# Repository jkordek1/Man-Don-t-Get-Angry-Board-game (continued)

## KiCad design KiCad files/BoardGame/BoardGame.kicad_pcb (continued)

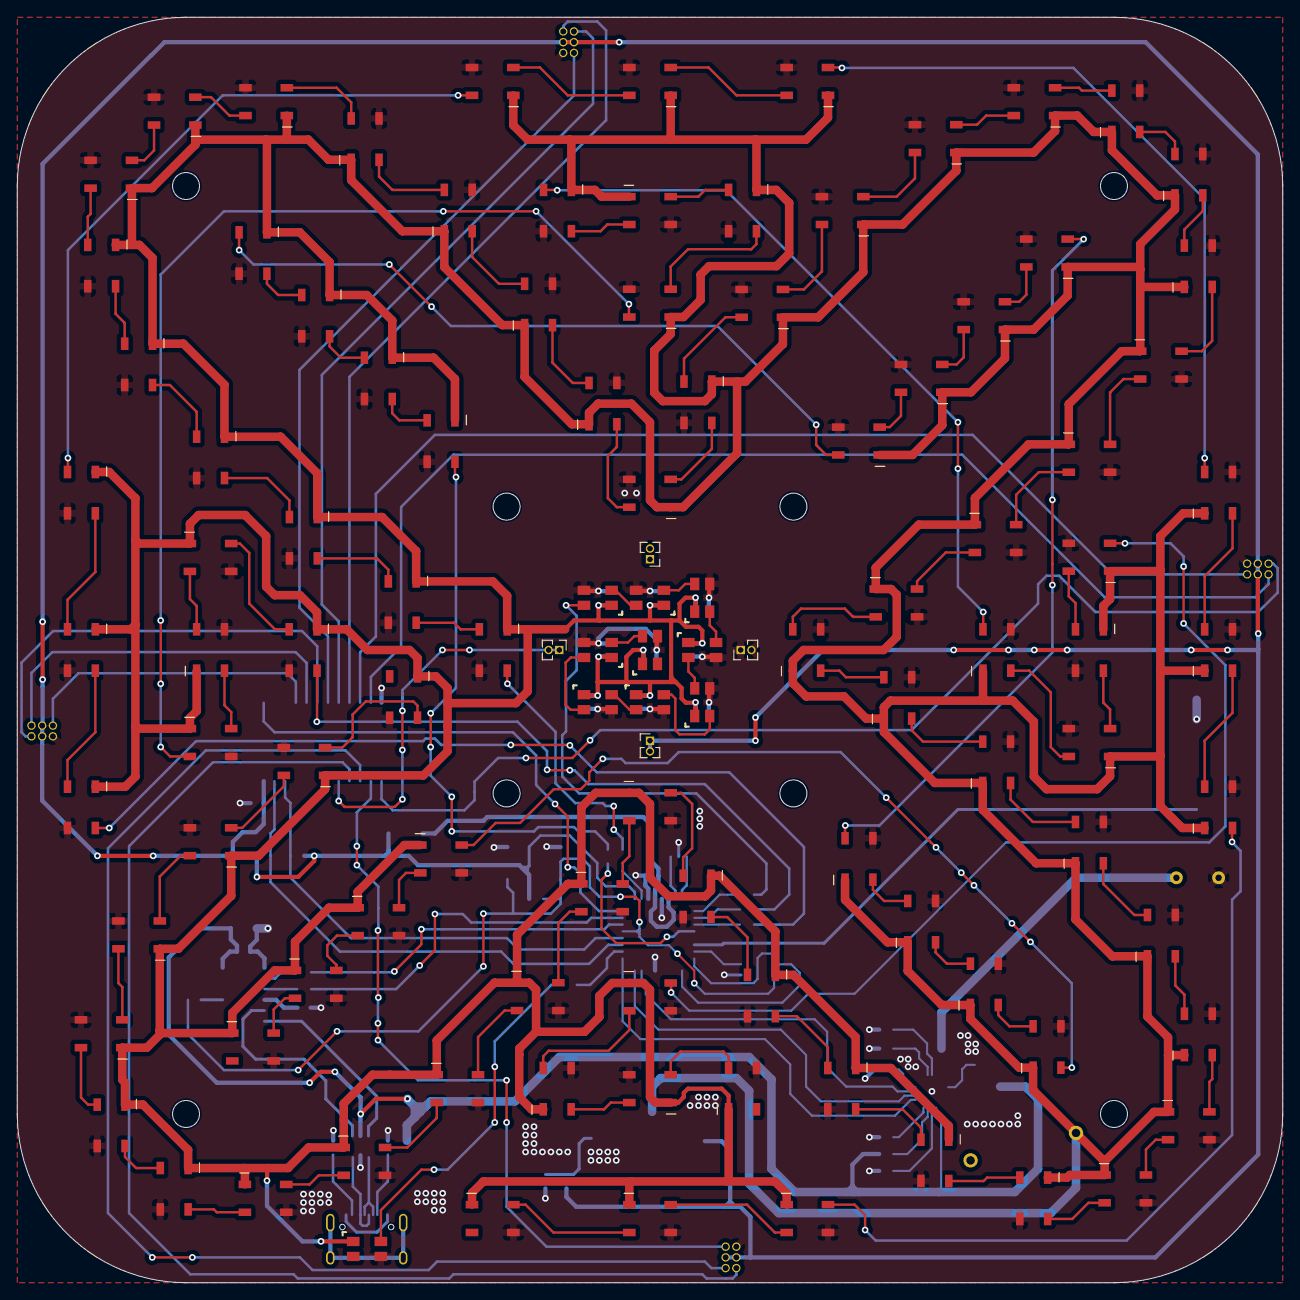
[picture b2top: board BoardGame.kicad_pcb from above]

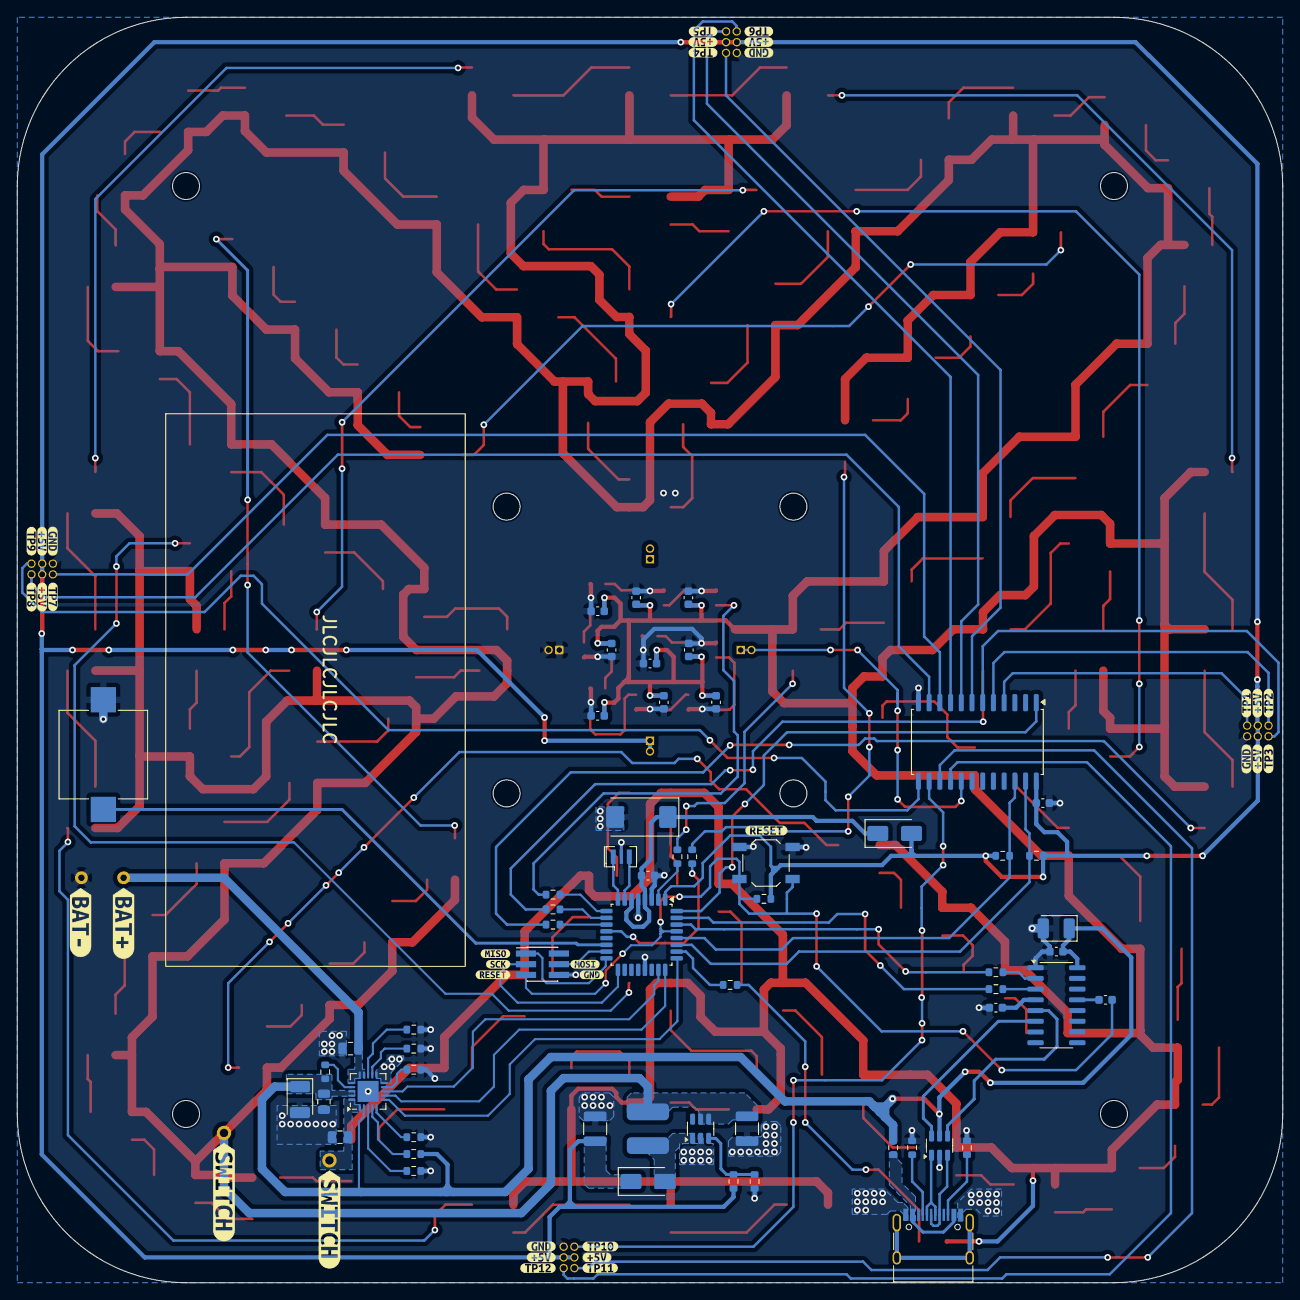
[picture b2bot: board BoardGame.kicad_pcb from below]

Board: 2 copper layers, 150.0 x 150.0 mm, 218 parts (94 on the bottom side), 167 nets.

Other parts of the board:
kibuzzard-635B9A1E, kibuzzard-635B9A1E#2: G***; kibuzzard-635B9A1E
kibuzzard-635BA7B4: G***; kibuzzard-635BA7B4
kibuzzard-635BA762: G***; kibuzzard-635BA762
kibuzzard-635CF4BC: G***; kibuzzard-635CF4BC
kibuzzard-635CF4CF: G***; kibuzzard-635CF4CF
kibuzzard-635CF4E4: G***; kibuzzard-635CF4E4
kibuzzard-635CF6FA, kibuzzard-635CF6FA#2, kibuzzard-635CF6FA#3, kibuzzard-635CF6FA#4: G***; kibuzzard-635CF6FA
kibuzzard-635CF7DB: G***; kibuzzard-635CF7DB
kibuzzard-635CF483: G***; kibuzzard-635CF483
kibuzzard-635CF507: G***; kibuzzard-635CF507
kibuzzard-635CF752, kibuzzard-635CF752#2, kibuzzard-635CF752#3, kibuzzard-635CF752#4, kibuzzard-635CF752#5, kibuzzard-635CF752#6, kibuzzard-635CF752#7, kibuzzard-635CF752#8: G***; kibuzzard-635CF752
kibuzzard-635CF795: G***; kibuzzard-635CF795
kibuzzard-635CF884: G***; kibuzzard-635CF884
kibuzzard-635CFA5F: G***; kibuzzard-635CFA5F
kibuzzard-635CFA8A: G***; kibuzzard-635CFA8A
kibuzzard-635CFAA6: G***; kibuzzard-635CFAA6
kibuzzard-635CFAF1: G***; kibuzzard-635CFAF1
kibuzzard-635CFB05: G***; kibuzzard-635CFB05
kibuzzard-635CFB13: G***; kibuzzard-635CFB13
kibuzzard-635CFD4A: G***; kibuzzard-635CFD4A
kibuzzard-635CFDAF: G***; kibuzzard-635CFDAF
kibuzzard-635CFDBF: G***; kibuzzard-635CFDBF
kibuzzard-636375F6: G***; kibuzzard-636375F6

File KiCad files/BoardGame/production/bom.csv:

Designator,Footprint,Quantity,Value,LCSC Part #
BT301,battery_103565_3000mah,1,Battery_Cell,-
"C1001, C1002, C1003, C1004, C1005, C1006, C1007, C1008, C1009, C201, C202, C204, C401, C501",0603,14,100n,C113803
C203,CP_EIA-3528-21_Kemet-B,1,10u,C2798040
C301,CP_EIA-3528-21_Kemet-B,1,4u7/25V,C2798040
"C302, C303, C304",0805,3,10u,C237493
C502,CP_EIA-7343-31_Kemet-D,1,1500uF,
"C601, C602",1210,2,22u / 16V,C337451
"D1001, D1002, D1003, D1004, D1005, D1006, D1007, D1008, D1009, D1010, D1011, D1012, D1013, D1014, D1015, D1016, D1017, D1018, D1019, D1020, D1021, D1022, D1023, D1024, D1025, D1026, D1027, D1028, D1029, D1030, D1031, D1032, D1033, D1034, D1035, D1036, D1037, D1038, D1039, D1040, D1041, D1042, D1043, D1044, D1045, D1046, D1047, D1048, D1049, D1050, D1051, D1052, D1053, D1054, D1055, D1056, D1057, D1058, D1059, D1060, D1061, D1062, D1063, D1064, D1065, D1066, D1067, D1068, D1069, D1070, D1071, D1072, D1073, D1074, D1075, D1076, D1077, D1078, D1079, D1080, D1081, D1082, D1083, D1084, D1085, D1086, D1087, D1088, D1089, D1090, D1091, D1092, D1093, D1094, D1095, D1096",LED_WS2812B_edited,96,WS2812B,-
"D1097, D1098, D1099, D1100, D1101, D1102, D1103, D1104, D1105",WS2812-mini,9,WS2812B,C527089
D1106,WS2812-mini,1,WS2812B,-
"D501, D601",D_SMA,2,SS12,C2985002
FB201,0603,1,100 @ 100MHz,C107332
"H1001, H1002, H1003, H1004, H1005, H1006, H1007, H1008",MountingHole_3.2mm_M3,8,MountingHole,
J201,USB_C_Receptacle_HRO_TYPE-C-31-M-12,1,USB_C_Receptacle_USB2.0,-
"J301, J302",PinHeader_1x01,2,Conn_01x01,-
"J401, J402, J403, J404",2x03_P1.27mm_conn,4,Conn_02x03_Odd_Even,-
"J405, J406, J407, J408",PinHeader_1x02_P1.27mm_Vertical,4,Conn_01x02_Female,
J501,PinHeader_2x03_P1.27mm_Vertical_SMD,1,USBasp,-
L601,Inductor_4mm(5x5mm pads),1,4R7,
LS501,KLJ-1102,1,Buzzer,
"R1001, R1002, R1003, R1004, R1005, R1006",0603,6,470R,
"R201, R204",0603,2,1k,
"R202, R203",0603,2,5k1,C3017721
"R301, R303, R307, R308, R310, R501",0603,6,10k,
R302,0603,1,2k,C25590
"R305, R601",0603,2,100k,
"R401, R402",0603,2,4k7,C114662
R602,0603,1,13k3,C185373
SW501,SW_SPST_TL3342,1,SW_Push,C2886894
U201,SOT-23-6,1,USBLC6-2SC6,C3029034
U202,SOIC-16_3.9x9.9mm_P1.27mm,1,CH340C,
U301,QFN-20-1EP_4x4mm_P0.5mm_EP2.5x2.5mm,1,MCP73871-2CC,
U401,SOIC-24W_7.5x15.4mm_P1.27mm,1,PCF8575,
U501,TQFP-32_7x7mm_P0.8mm,1,ATmega328P-A,
U601,SOT-23-6,1,MT3608,C2932326
Y501,CSTCE16M0V53-R0,1,16MHz,C32180

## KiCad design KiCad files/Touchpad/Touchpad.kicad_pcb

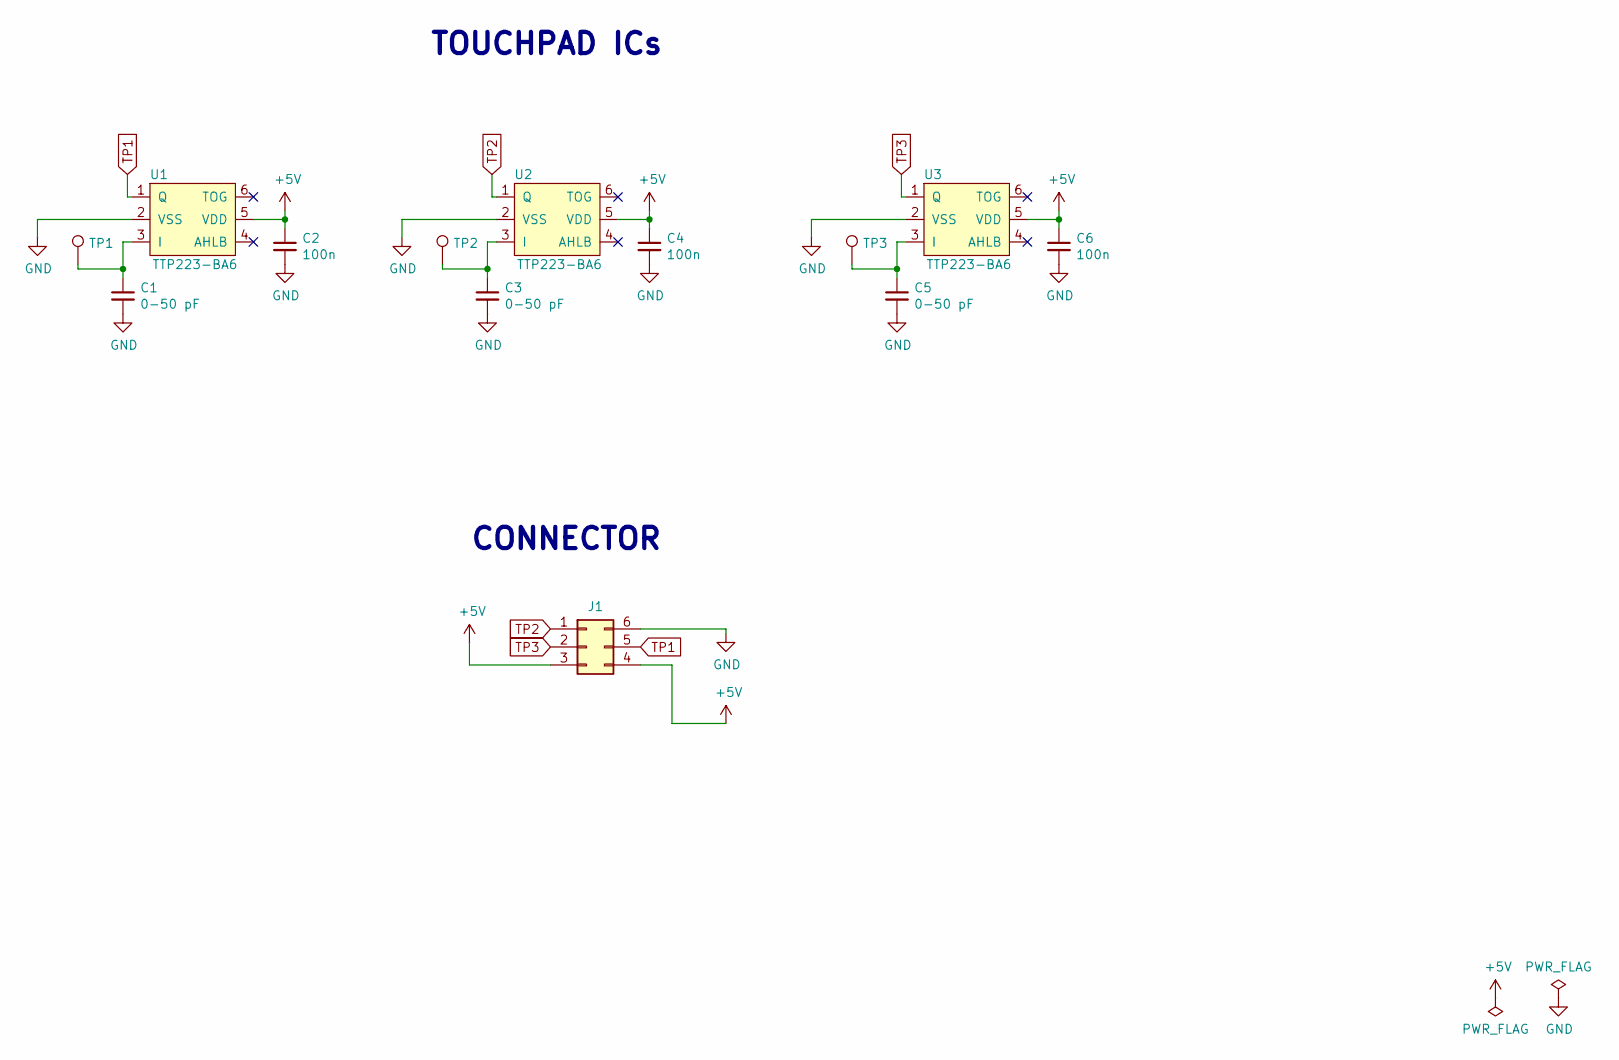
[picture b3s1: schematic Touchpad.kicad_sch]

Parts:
C1, C3, C5: 0-50 pF; C_0603_1608Metric
C2, C4, C6: 100n; C_0603_1608Metric
J1: Conn_02x03_Counter_Clockwise; PinHeader_2x03_P1.27mm_Vertical_SMD
TP1: TestPoint; TP_11mm_kvacica
TP2: TestPoint; TP_11mm_strelicaLijevo
TP3: TestPoint; TP_11mm_strelicaDesno
U1, U2, U3: TTP223-BA6; SOT-23-6

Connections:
+5V: C2.1, C4.1, C6.1, J1.3, J1.4, U1.5 (VDD), U2.5 (VDD), U3.5 (VDD)
GND: C1.2, C2.2, C3.2, C4.2, C5.2, C6.2, J1.6, U1.2 (VSS), U2.2 (VSS), U3.2 (VSS)
unnamed: C1.1, TP1.1, U1.3 (I)
unnamed: C3.1, TP2.1, U2.3 (I)
unnamed: C5.1, TP3.1, U3.3 (I)
TP1: J1.5, U1.1 (Q)
TP2: J1.1, U2.1 (Q)
TP3: J1.2, U3.1 (Q)

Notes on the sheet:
TOUCHPAD ICs
CONNECTOR

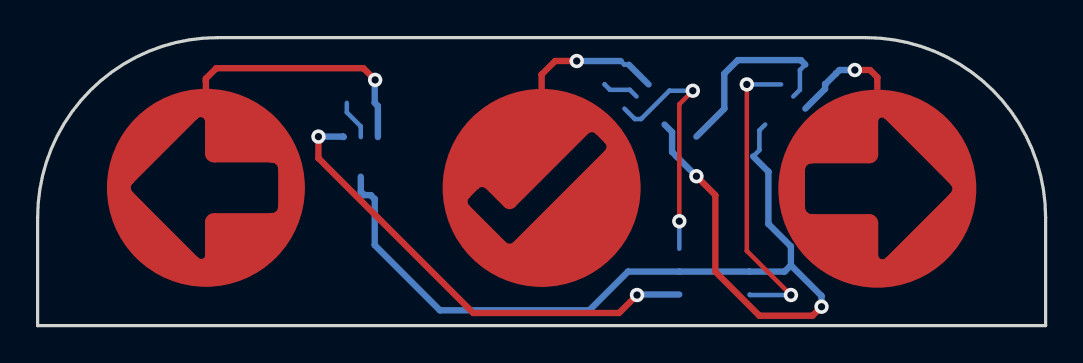
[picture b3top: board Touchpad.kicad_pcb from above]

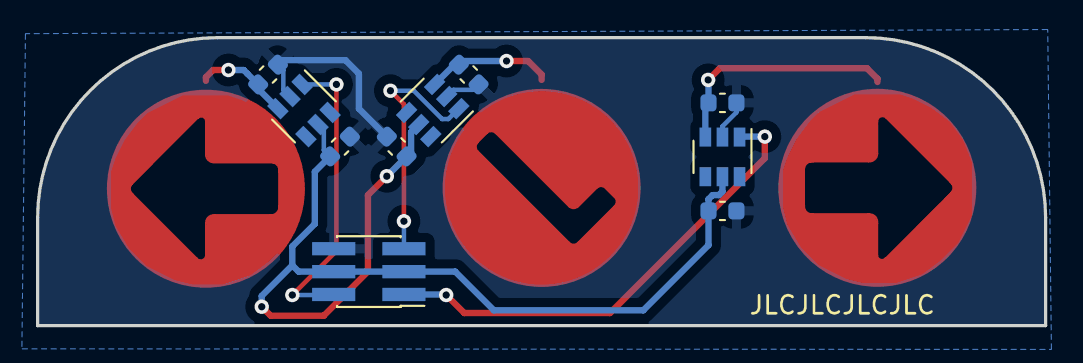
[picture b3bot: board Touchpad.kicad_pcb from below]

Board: 2 copper layers, 56.0 x 16.0 mm, 13 parts (10 on the bottom side), 8 nets.

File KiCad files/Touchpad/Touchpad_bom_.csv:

Component,Description,Part,References,Value,Footprint,Quantity Per PCB,Datasheet
1,"Unpolarized capacitor, small symbol",C_Small,C2 C4 C6,100n,C_0603_1608Metric,3,~
2,"Unpolarized capacitor, small symbol",C_Small,C1 C3 C5,0-50 pF,C_0603_1608Metric,3,~
3,"Generic connector, double row, 02x03, counter clockwise pin numbering scheme (similar to DIP packge numbering), script generated (kicad-library-utils/schlib/autogen/connector/)",Conn_02x03_Counter_Clockwise,J1,Conn_02x03_Counter_Clockwise,PinHeader_2x03_P1.27mm_Vertical_SMD,1,~
4,,TTP223-BA6,U1 U2 U3,TTP223-BA6,SOT-23-6,3,





Component Groups:,4
Component Count:,10
Fitted Components:,10
Number of PCBs:,1
Total components:,10
Schematic Version:,
Schematic Date:,
PCB Variant:,default
BoM Date:,10.1.2023. 13:06:24
Schematic Source:,Touchpad.kicad_sch
KiCad Version:,Eeschema (6.0.10)

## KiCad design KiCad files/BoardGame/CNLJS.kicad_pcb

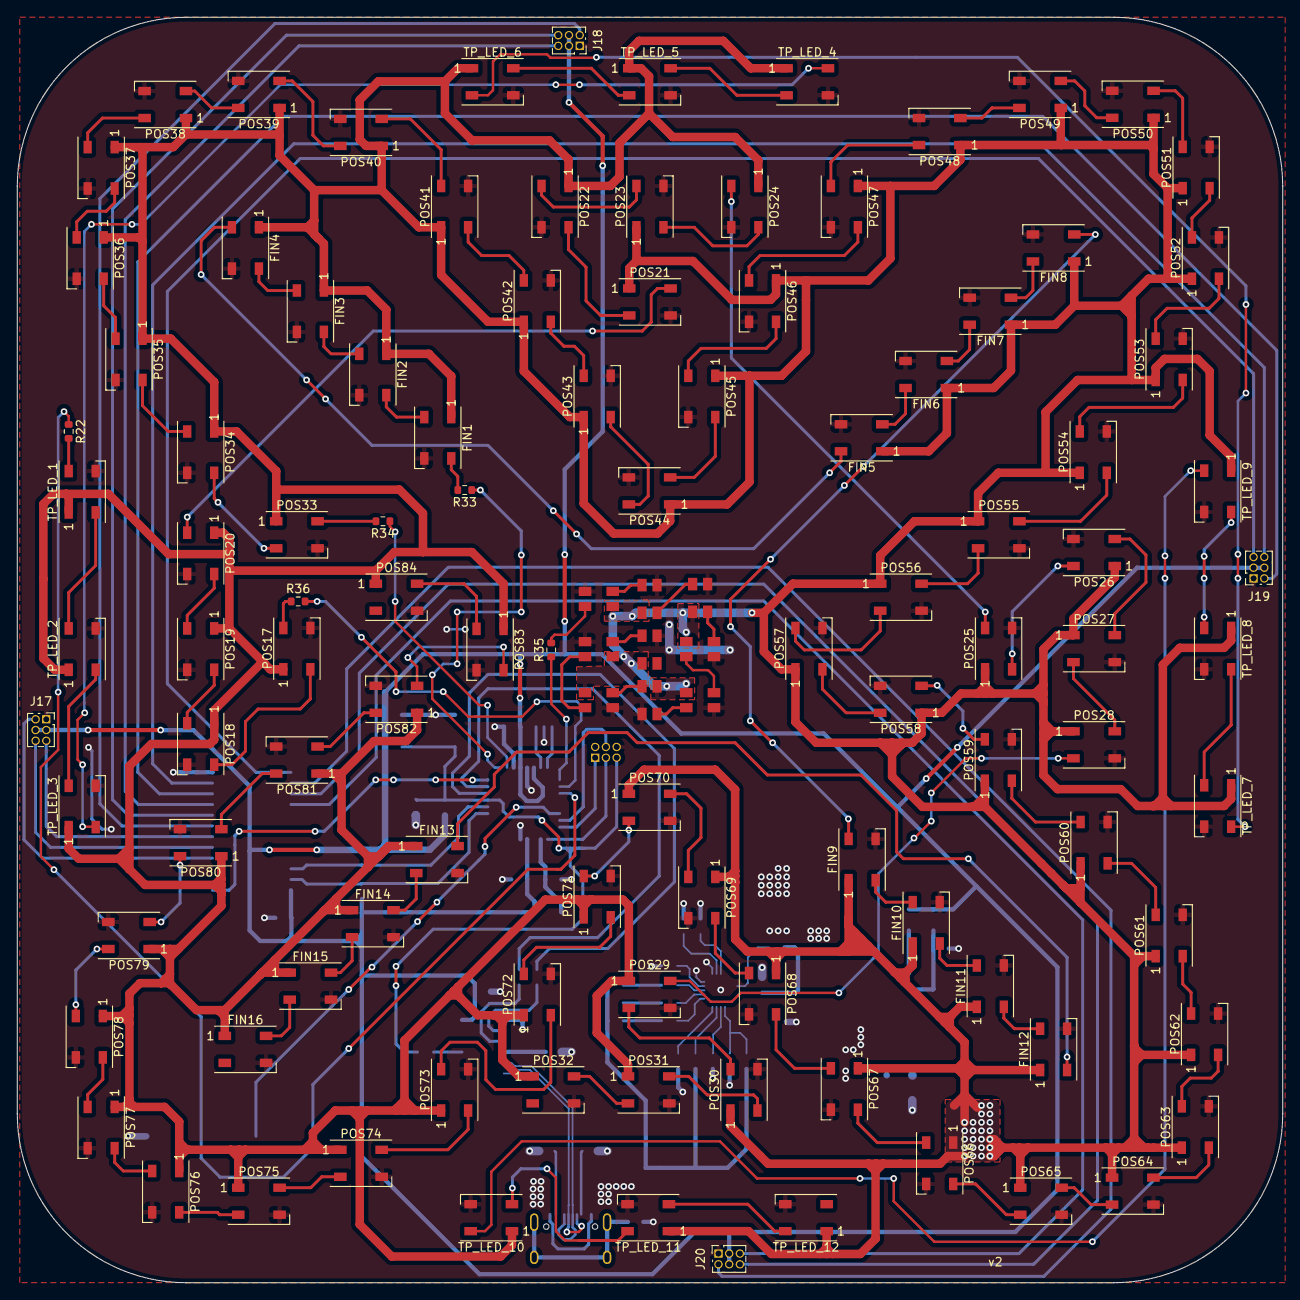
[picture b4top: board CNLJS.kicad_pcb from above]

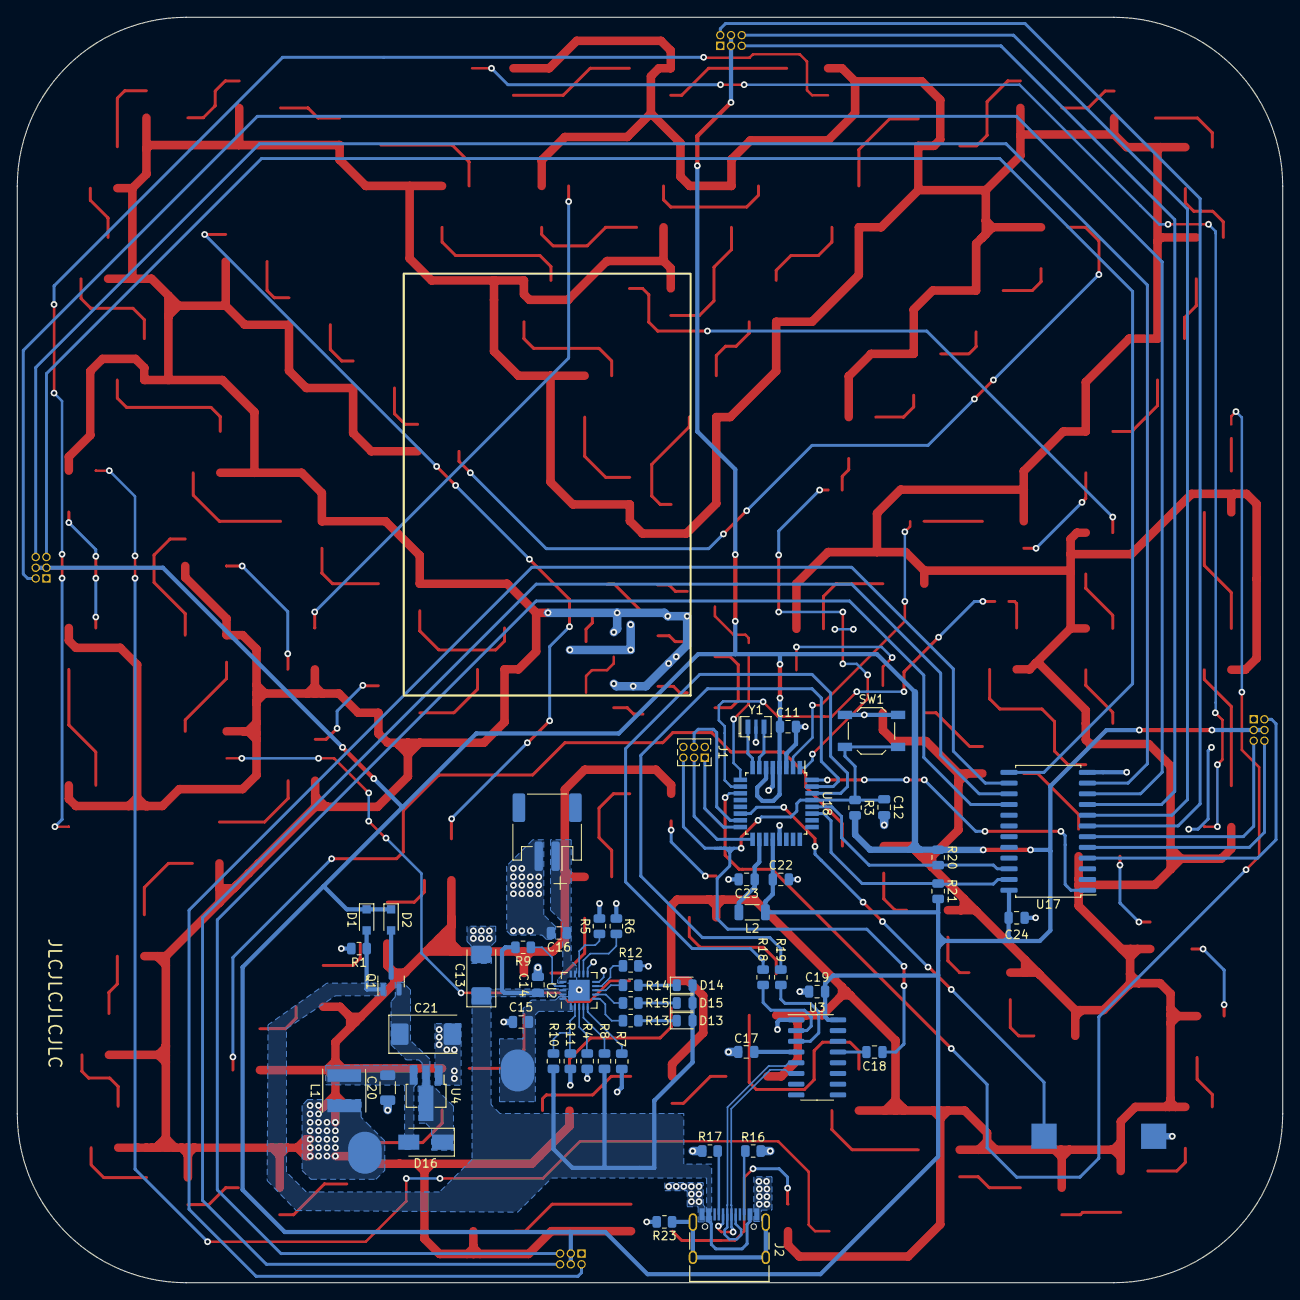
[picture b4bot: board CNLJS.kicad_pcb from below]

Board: 2 copper layers, 150.0 x 150.0 mm, 171 parts (57 on the bottom side), 167 nets.

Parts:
BT1: Battery_Cell; JST_PH_S2B-PH-SM4-TB_1x02-1MP_P2.00mm_Horizontal
C11, C18, C19, C22, C23, C24: 100n; C_0805_2012Metric
C12: 1u; C_0805_2012Metric
C13: 4.7u / 25V; CP_EIA-6032-28_Kemet-C
C14, C15, C16: 10u; C_0805_2012Metric
C17: 10n; C_0805_2012Metric
C20: 47u; C_1206_3216Metric
C21: 47u / 10V; CP_EIA-7343-30_AVX-N
D1, D2: B5819WS; D_SOD-323_HandSoldering
D13, D14, D15: LED_Small; LED_0805_2012Metric
D16: SS14; D_SMA
FIN1, FIN2, FIN3, FIN4, FIN5, FIN6, FIN7, FIN8, FIN9, FIN10, FIN11, FIN12, FIN13, FIN14, FIN15, FIN16: WS2812-4020_dual; LED_WS2812B_PLCC4_5.0x5.0mm_P3.2mm
J1: USBasp; PinSocket_2x03_P1.27mm_Vertical
J2: USB_C_Receptacle_USB2.0; USB_C_Receptacle_HRO_TYPE-C-31-M-12
J17, J18, J19, J20: Conn_02x03_Odd_Even; PinSocket_2x03_P1.27mm_Vertical
J21, J22: Conn_01x01; Padovi_sklopke
L1: 47uH; L_Taiyo-Yuden_NR-50xx
L2: 10u; L_1206_3216Metric
LED1, LED2, LED3, LED4, LED5, LED6, LED7, LED8, LED9: WS2812-4020_single; WS2812-mini
LS1: Buzzer; KLJ-1102
POS17, POS18, POS19, POS20, POS21, POS22, POS23, POS24, POS25, POS26, POS27, POS28, POS29, POS30, POS31, POS32, POS33, POS34, POS35, POS36, POS37, POS38, POS39, POS40, POS41, POS42, POS43, POS44, POS45, POS46, POS47, POS48, POS49, POS50, POS51, POS52, POS53, POS54, POS55, POS56, POS57, POS58, POS59, POS60, POS61, POS62, POS63, POS64, POS65, POS66, POS67, POS68, POS69, POS70, POS71, POS72, POS73, POS74, POS75, POS76, POS77, POS78, POS79, POS80, POS81, POS82, POS83, POS84: WS2812-4020_dual; LED_WS2812B_PLCC4_5.0x5.0mm_P3.2mm
Q1: Si2319CDS; SOT-23
R1, R3, R4, R7, R8, R9, R12: 10k; R_0805_2012Metric
R5: 2k; R_0805_2012Metric
R6, R11: 100k; R_0805_2012Metric
R10: 270k; R_0805_2012Metric
R13, R14, R15, R18, R19: 1k; R_0805_2012Metric
R16, R17: 5k1; R_0805_2012Metric
R20, R21: 4k7; R_0805_2012Metric
R22, R33, R34, R35, R36: 470R; R_0603_1608Metric
R23: 1M; R_0805_2012Metric
SW1: SW_Push; SW_SPST_TL3342
TP_LED_1, TP_LED_2, TP_LED_3, TP_LED_4, TP_LED_5, TP_LED_6, TP_LED_7, TP_LED_8, TP_LED_9, TP_LED_10, TP_LED_11, TP_LED_12: WS2812-4020_dual; LED_WS2812B_PLCC4_5.0x5.0mm_P3.2mm
U2: MCP73871-2CC; QFN-20-1EP_4x4mm_P0.5mm_EP2.5x2.5mm
U3: CH340C; SOIC-16_3.9x9.9mm_P1.27mm
U4: 2108; SOT-89-3_Handsoldering
U17: PCF8575; SOIC-24W_7.5x15.4mm_P1.27mm
U18: ATmega328-A; TQFP-32_7x7mm_P0.8mm
Y1: 16MHz; CSTCE16M0V53-R0

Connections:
+BATT: BT1.1 (+), C16.1, U2.14 (VBAT), U2.15 (VBAT), U2.16 (Vbat_SENSE)
/LEDs/Cube (9LEDs)/Cube-LEDs: LED1.4 (DIN), R35.2
/LEDs/Finish (16LEDs)/Finish-LEDs: FIN1.4 (DIN), R33.2
/LEDs/Positions (52LEDs)/Positions-LEDs: POS33.4 (DIN), R34.2
/LEDs/Start (16LEDs)/Start-LEDs: POS17.4 (DIN), R36.2
/Power/CH_OUT: C15.1, J22.1, U2.1 (OUT), U2.20 (OUT)
D+: J2.A6 (D+), J2.B6 (D+), U3.5 (UD+)
D-: J2.A7 (D-), J2.B7 (D-), U3.6 (UD-)
GND: BT1.2 (-), C11.2, C12.2, C13.2, C14.2, C15.2, C16.2, C17.2, C19.2, C20.2, C21.2, C22.2, C23.2, C24.2, FIN1.3 (VSS), FIN2.3 (VSS), FIN3.3 (VSS), FIN4.3 (VSS), FIN5.3 (VSS), FIN6.3 (VSS), FIN7.3 (VSS), FIN8.3 (VSS), FIN9.3 (VSS), FIN10.3 (VSS), FIN11.3 (VSS), FIN12.3 (VSS), FIN13.3 (VSS), FIN14.3 (VSS), FIN15.3 (VSS), FIN16.3 (VSS), J1.6, J2.A1 (GND), J2.A12 (GND), J2.B1 (GND), J2.B12 (GND), J17.1, J18.1, J19.1, J20.1, LED1.3 (VSS), LED2.3 (VSS), LED3.3 (VSS), LED4.3 (VSS), LED5.3 (VSS), LED6.3 (VSS), LED7.3 (VSS), LED8.3 (VSS), LED9.3 (VSS), LS1.2, POS17.3 (VSS), POS18.3 (VSS), POS19.3 (VSS), POS20.3 (VSS), POS21.3 (VSS), POS22.3 (VSS), POS23.3 (VSS), POS24.3 (VSS), POS25.3 (VSS), POS26.3 (VSS), POS27.3 (VSS), POS28.3 (VSS), POS29.3 (VSS), POS30.3 (VSS), POS31.3 (VSS), POS32.3 (VSS), POS33.3 (VSS), POS34.3 (VSS), POS35.3 (VSS), POS36.3 (VSS), POS37.3 (VSS), POS38.3 (VSS), POS39.3 (VSS), POS40.3 (VSS), POS41.3 (VSS), POS42.3 (VSS), POS43.3 (VSS), POS44.3 (VSS), POS45.3 (VSS), POS46.3 (VSS), POS47.3 (VSS), POS48.3 (VSS), POS49.3 (VSS), POS50.3 (VSS), POS51.3 (VSS), POS52.3 (VSS), POS53.3 (VSS), POS54.3 (VSS), POS55.3 (VSS), POS56.3 (VSS), POS57.3 (VSS), POS58.3 (VSS), POS59.3 (VSS), POS60.3 (VSS), POS61.3 (VSS), POS62.3 (VSS), POS63.3 (VSS), POS64.3 (VSS), POS65.3 (VSS), POS66.3 (VSS), POS67.3 (VSS), POS68.3 (VSS), POS69.3 (VSS), POS70.3 (VSS), POS71.3 (VSS), POS72.3 (VSS), POS73.3 (VSS), POS74.3 (VSS), POS75.3 (VSS), POS76.3 (VSS), POS77.3 (VSS), POS78.3 (VSS), POS79.3 (VSS), POS80.3 (VSS), POS81.3 (VSS), POS82.3 (VSS), POS83.3 (VSS), POS84.3 (VSS), R1.2, R4.2, R5.2, R6.2, R7.2, R11.2, R12.2, R16.2, R17.2, R23.2, SW1.1, TP_LED_1.3 (VSS), TP_LED_2.3 (VSS), TP_LED_3.3 (VSS), TP_LED_4.3 (VSS), TP_LED_5.3 (VSS), TP_LED_6.3 (VSS), TP_LED_7.3 (VSS), TP_LED_8.3 (VSS), TP_LED_9.3 (VSS), TP_LED_10.3 (VSS), TP_LED_11.3 (VSS), TP_LED_12.3 (VSS), U2.10 (VSS), U2.11 (VSS), U2.21 (VSS), U3.1 (GND), U4.1 (GND), U17.12 (GND), U18.3 (GND), U18.5 (GND), U18.21 (GND), Y1.2
INT: U17.1 (~INT), U18.32 (PD2)
MISO: J1.1, U18.16 (PB4)
MOSI: J1.4, U18.15 (PB3)
NP_1: R33.1, U18.1 (PD3)
NP_2: R34.1, U18.2 (PD4)
NP_3: R35.1, U18.9 (PD5)
NP_4: R36.1, U18.10 (PD6)
NP_5: R22.1, U18.11 (PD7)
unnamed: C17.1, U3.4 (V3)
unnamed: C18.2, U3.13 (~DTR)
unnamed: C20.1, D16.2 (A), L1.2, U4.3 (VIN)
unnamed: C21.1, D16.1 (K), Q1.2 (S), U4.2 (VOUT)
unnamed: C23.1, L2.2, U18.18 (AVCC)
unnamed: D2.2 (A), Q1.3 (D)
unnamed: D13.1 (K), R13.1
unnamed: D14.1 (K), R14.1
unnamed: D15.1 (K), R15.1
unnamed: FIN1.2 (DOUT), FIN2.4 (DIN)
unnamed: FIN2.2 (DOUT), FIN3.4 (DIN)
unnamed: FIN3.2 (DOUT), FIN4.4 (DIN)
unnamed: FIN4.2 (DOUT), FIN5.4 (DIN)
unnamed: FIN5.2 (DOUT), FIN6.4 (DIN)
unnamed: FIN6.2 (DOUT), FIN7.4 (DIN)
unnamed: FIN7.2 (DOUT), FIN8.4 (DIN)
unnamed: FIN8.2 (DOUT), FIN9.4 (DIN)
unnamed: FIN10.2 (DOUT), FIN11.4 (DIN)
unnamed: FIN9.2 (DOUT), FIN10.4 (DIN)
unnamed: FIN11.2 (DOUT), FIN12.4 (DIN)
unnamed: FIN12.2 (DOUT), FIN13.4 (DIN)
unnamed: FIN13.2 (DOUT), FIN14.4 (DIN)
unnamed: FIN14.2 (DOUT), FIN15.4 (DIN)
unnamed: FIN15.2 (DOUT), FIN16.4 (DIN)
unnamed: J2.A5 (CC1), R17.1
unnamed: J2.B5 (CC2), R16.1
unnamed: J2.S1 (SHIELD), R23.1
unnamed: LED1.2 (DOUT), LED2.4 (DIN)
unnamed: LED2.2 (DOUT), LED3.4 (DIN)
unnamed: LED3.2 (DOUT), LED4.4 (DIN)
unnamed: LED4.2 (DOUT), LED5.4 (DIN)
unnamed: LED5.2 (DOUT), LED6.4 (DIN)
unnamed: LED6.2 (DOUT), LED7.4 (DIN)
unnamed: LED7.2 (DOUT), LED8.4 (DIN)
unnamed: LED8.2 (DOUT), LED9.4 (DIN)
unnamed: LS1.1, U18.14 (PB2)
unnamed: POS17.2 (DOUT), POS18.4 (DIN)
unnamed: POS18.2 (DOUT), POS19.4 (DIN)
unnamed: POS19.2 (DOUT), POS20.4 (DIN)
unnamed: POS20.2 (DOUT), POS21.4 (DIN)
unnamed: POS21.2 (DOUT), POS22.4 (DIN)
unnamed: POS22.2 (DOUT), POS23.4 (DIN)
unnamed: POS23.2 (DOUT), POS24.4 (DIN)
unnamed: POS24.2 (DOUT), POS25.4 (DIN)
unnamed: POS25.2 (DOUT), POS26.4 (DIN)
unnamed: POS26.2 (DOUT), POS27.4 (DIN)
unnamed: POS27.2 (DOUT), POS28.4 (DIN)
unnamed: POS28.2 (DOUT), POS29.4 (DIN)
unnamed: POS29.2 (DOUT), POS30.4 (DIN)
unnamed: POS30.2 (DOUT), POS31.4 (DIN)
unnamed: POS31.2 (DOUT), POS32.4 (DIN)
unnamed: POS33.2 (DOUT), POS34.4 (DIN)
unnamed: POS34.2 (DOUT), POS35.4 (DIN)
unnamed: POS35.2 (DOUT), POS36.4 (DIN)
unnamed: POS36.2 (DOUT), POS37.4 (DIN)
unnamed: POS37.2 (DOUT), POS38.4 (DIN)
unnamed: POS38.2 (DOUT), POS39.4 (DIN)
unnamed: POS39.2 (DOUT), POS40.4 (DIN)
unnamed: POS40.2 (DOUT), POS41.4 (DIN)
unnamed: POS41.2 (DOUT), POS42.4 (DIN)
unnamed: POS42.2 (DOUT), POS43.4 (DIN)
unnamed: POS43.2 (DOUT), POS44.4 (DIN)
unnamed: POS44.2 (DOUT), POS45.4 (DIN)
unnamed: POS45.2 (DOUT), POS46.4 (DIN)
unnamed: POS46.2 (DOUT), POS47.4 (DIN)
unnamed: POS47.2 (DOUT), POS48.4 (DIN)
unnamed: POS48.2 (DOUT), POS49.4 (DIN)
unnamed: POS49.2 (DOUT), POS50.4 (DIN)
unnamed: POS50.2 (DOUT), POS51.4 (DIN)
unnamed: POS51.2 (DOUT), POS52.4 (DIN)
unnamed: POS52.2 (DOUT), POS53.4 (DIN)
unnamed: POS53.2 (DOUT), POS54.4 (DIN)
unnamed: POS54.2 (DOUT), POS55.4 (DIN)
unnamed: POS55.2 (DOUT), POS56.4 (DIN)
unnamed: POS56.2 (DOUT), POS57.4 (DIN)
unnamed: POS57.2 (DOUT), POS58.4 (DIN)
unnamed: POS58.2 (DOUT), POS59.4 (DIN)
unnamed: POS59.2 (DOUT), POS60.4 (DIN)
unnamed: POS60.2 (DOUT), POS61.4 (DIN)
unnamed: POS61.2 (DOUT), POS62.4 (DIN)
unnamed: POS62.2 (DOUT), POS63.4 (DIN)
unnamed: POS63.2 (DOUT), POS64.4 (DIN)
unnamed: POS64.2 (DOUT), POS65.4 (DIN)
unnamed: POS65.2 (DOUT), POS66.4 (DIN)
unnamed: POS66.2 (DOUT), POS67.4 (DIN)
unnamed: POS67.2 (DOUT), POS68.4 (DIN)
unnamed: POS68.2 (DOUT), POS69.4 (DIN)
unnamed: POS69.2 (DOUT), POS70.4 (DIN)
unnamed: POS70.2 (DOUT), POS71.4 (DIN)
unnamed: POS71.2 (DOUT), POS72.4 (DIN)
unnamed: POS72.2 (DOUT), POS73.4 (DIN)
unnamed: POS73.2 (DOUT), POS74.4 (DIN)
unnamed: POS74.2 (DOUT), POS75.4 (DIN)
unnamed: POS75.2 (DOUT), POS76.4 (DIN)
unnamed: POS76.2 (DOUT), POS77.4 (DIN)
unnamed: POS77.2 (DOUT), POS78.4 (DIN)
unnamed: POS78.2 (DOUT), POS79.4 (DIN)
unnamed: POS79.2 (DOUT), POS80.4 (DIN)
unnamed: POS80.2 (DOUT), POS81.4 (DIN)
unnamed: POS81.2 (DOUT), POS82.4 (DIN)
unnamed: POS82.2 (DOUT), POS83.4 (DIN)
unnamed: POS83.2 (DOUT), POS84.4 (DIN)
unnamed: R4.1, U2.3 (SEL)
unnamed: R5.1, U2.13 (PROG1)
unnamed: R6.1, U2.12 (PROG3)
unnamed: R7.1, U2.5 (THERM)
unnamed: R8.1, U2.4 (PROG2)
unnamed: R9.1, U2.17 (CE)
unnamed: R10.2, R11.1, U2.2 (VPCC)
unnamed: R12.1, U2.9 (~TE)
unnamed: R13.2, U2.6 (~PG)
unnamed: R14.2, U2.8 (STAT1/~LBO)
unnamed: R15.2, U2.7 (STAT2)
unnamed: R18.2, U3.2 (TXD)
unnamed: R19.2, U3.3 (RXD)
unnamed: R22.2, TP_LED_1.4 (DIN)
unnamed: TP_LED_1.2 (DOUT), TP_LED_2.4 (DIN)
unnamed: TP_LED_2.2 (DOUT), TP_LED_3.4 (DIN)
unnamed: TP_LED_3.2 (DOUT), TP_LED_4.4 (DIN)
unnamed: TP_LED_4.2 (DOUT), TP_LED_5.4 (DIN)
unnamed: TP_LED_5.2 (DOUT), TP_LED_6.4 (DIN)
unnamed: TP_LED_6.2 (DOUT), TP_LED_7.4 (DIN)
unnamed: TP_LED_7.2 (DOUT), TP_LED_8.4 (DIN)
unnamed: TP_LED_8.2 (DOUT), TP_LED_9.4 (DIN)
unnamed: TP_LED_10.2 (DOUT), TP_LED_11.4 (DIN)
unnamed: TP_LED_9.2 (DOUT), TP_LED_10.4 (DIN)
unnamed: TP_LED_11.2 (DOUT), TP_LED_12.4 (DIN)
unnamed: U18.7 (XTAL1/PB6), Y1.3
unnamed: U18.8 (XTAL2/PB7), Y1.1
RESET: C12.1, C18.1, J1.5, R3.1, SW1.2, U18.29 (~RESET/PC6)
RX: R18.1, U18.30 (PD0)
SCK: J1.3, U18.17 (PB5)
SCL: R20.2, U17.22 (SCL), U18.28 (PC5)
SDA: R21.2, U17.23 (SDA), U18.27 (PC4)
TP_1: J17.2, U17.4 (P00)
TP_2: J17.6, U17.5 (P01)
TP_3: J17.5, U17.6 (P02)
TP_4: J18.2, U17.7 (P03)
TP_5: J18.6, U17.8 (P04)
TP_6: J18.5, U17.9 (P05)
TP_7: J19.2, U17.10 (P06)
TP_8: J19.6, U17.11 (P07)
TP_9: J19.5, U17.13 (P10)
TP_10: J20.2, U17.14 (P11)
TP_11: J20.6, U17.15 (P12)
TP_12: J20.5, U17.16 (P13)
TX: R19.1, U18.31 (PD1)
VBUS: C13.1, C14.1, D1.2 (A), D13.2 (A), D14.2 (A), D15.2 (A), J2.A4 (VBUS), J2.A9 (VBUS), J2.B4 (VBUS), J2.B9 (VBUS), Q1.1 (G), R1.1, R8.2, R9.2, R10.1, U2.18 (IN), U2.19 (IN)
VCC: FIN1.1 (VDD), FIN2.1 (VDD), FIN3.1 (VDD), FIN4.1 (VDD), FIN5.1 (VDD), FIN6.1 (VDD), FIN7.1 (VDD), FIN8.1 (VDD), FIN9.1 (VDD), FIN10.1 (VDD), FIN11.1 (VDD), FIN12.1 (VDD), FIN13.1 (VDD), FIN14.1 (VDD), FIN15.1 (VDD), FIN16.1 (VDD), J21.1, L1.1, LED1.1 (VDD), LED2.1 (VDD), LED3.1 (VDD), LED4.1 (VDD), LED5.1 (VDD), LED6.1 (VDD), LED7.1 (VDD), LED8.1 (VDD), LED9.1 (VDD), POS17.1 (VDD), POS18.1 (VDD), POS19.1 (VDD), POS20.1 (VDD), POS21.1 (VDD), POS22.1 (VDD), POS23.1 (VDD), POS24.1 (VDD), POS25.1 (VDD), POS26.1 (VDD), POS27.1 (VDD), POS28.1 (VDD), POS29.1 (VDD), POS30.1 (VDD), POS31.1 (VDD), POS32.1 (VDD), POS33.1 (VDD), POS34.1 (VDD), POS35.1 (VDD), POS36.1 (VDD), POS37.1 (VDD), POS38.1 (VDD), POS39.1 (VDD), POS40.1 (VDD), POS41.1 (VDD), POS42.1 (VDD), POS43.1 (VDD), POS44.1 (VDD), POS45.1 (VDD), POS46.1 (VDD), POS47.1 (VDD), POS48.1 (VDD), POS49.1 (VDD), POS50.1 (VDD), POS51.1 (VDD), POS52.1 (VDD), POS53.1 (VDD), POS54.1 (VDD), POS55.1 (VDD), POS56.1 (VDD), POS57.1 (VDD), POS58.1 (VDD), POS59.1 (VDD), POS60.1 (VDD), POS61.1 (VDD), POS62.1 (VDD), POS63.1 (VDD), POS64.1 (VDD), POS65.1 (VDD), POS66.1 (VDD), POS67.1 (VDD), POS68.1 (VDD), POS69.1 (VDD), POS70.1 (VDD), POS71.1 (VDD), POS72.1 (VDD), POS73.1 (VDD), POS74.1 (VDD), POS75.1 (VDD), POS76.1 (VDD), POS77.1 (VDD), POS78.1 (VDD), POS79.1 (VDD), POS80.1 (VDD), POS81.1 (VDD), POS82.1 (VDD), POS83.1 (VDD), POS84.1 (VDD), TP_LED_1.1 (VDD), TP_LED_2.1 (VDD), TP_LED_3.1 (VDD), TP_LED_4.1 (VDD), TP_LED_5.1 (VDD), TP_LED_6.1 (VDD), TP_LED_7.1 (VDD), TP_LED_8.1 (VDD), TP_LED_9.1 (VDD), TP_LED_10.1 (VDD), TP_LED_11.1 (VDD), TP_LED_12.1 (VDD)
VDD: C11.1, C19.1, C22.1, C24.1, D1.1 (K), D2.1 (K), J17.3, J17.4, J18.3, J18.4, J19.3, J19.4, J20.3, J20.4, L2.1, R3.2, R20.1, R21.1, U3.16 (VCC), U17.24 (VCC), U18.4 (VCC), U18.6 (VCC), U18.20 (AREF)
